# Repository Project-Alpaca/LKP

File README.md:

# LKP

レンくんピアノ (Len-kun Piano)

Capacitive touch slider controller for rhythm games.

# Contents

## pcb/LKP-Core

Microcontroller board for use with LKP electrode boards. Supports up to 32 channel of self capacitance input. Includes a WS281x LED driver channel with protection resistor. Supports I2C or UART as communication methods.

For sample firmware for use with LKP-Core, see [LKP-FW](https://github.com/Project-Alpaca/LKP-FW).

### Pin mapping

I/O port:

| \#  | Description |
| --- | ----------- |
|  1  | GND |
|  2  | INT |
|  3  | SCL/RX |
|  4  | SDA/TX |

WS281x LED connector:

| \#  | Description |
| --- | ----------- |
|  1  | GND |
|  2  | LED |

SWD connector:

| \#  | Description |
| --- | ----------- |
|  1  | VTARG |
|  2  | GND |
|  3  | RESET |
|  4  | SWCLK |
|  5  | SWDIO |

## pcb/LKP-Core-EasyAccess

**IMPORTANT**: WS281x LED driver will not work on this variant. See errata. This variant is only included for documentation purposes and will no longer receive updates.

A variant of LKP-Core that originally focused on improved accessibility for arcade controller DIY hobbyists with only basic (through hole) soldering skills. All parts used in this variant (once the chip shortage situations improve) are available for use with [JLCPCB Assembly](https://jlcpcb.com/smt-assembly) service, thus enables the possibility of ordering fully assembled and working boards straight from JLCPCB. Even without the assembly service working at the moment, the chip used in this variant can be purchased from LCSC in low quantity for a lot less money compare to the original chip on Digi-key, so it also acts as a budget option without sacrificing performance in significant ways.

## pcb/LKP-Diva-Electrode-Tile

Electrode board for Project DIVA Future Tone slider controller. Works as a 2-tile setup. Both tiles use the same design, with right tile being a 180 degree rotated version of the left tile.

## pcb/LKP-Chu-Electrode-Tile

Electrode board for Chunithm slider controller. Works the same as its LKP-Diva counterpart.

## pcb/LKP-IF-QC

I2C quick connect (compatible with SparkFun [Qwiic®][qwiic] and Adafruit [STEMMA® QT][stemmaqt]) interface for LKP-Core. Goes up to 1MHz for I2C connections and up to 24MHz for UART connections. Converts between 5V logic used by LKP-Core and 3.3V logic used by Qwiic®/STEMMA® QT.

It is also possible to use it to convert UART signal for main microcontroller running between 1.65V and 3.6V. To set it up:

1. Break out the signals on any one of the Qwiic®/STEMMA® QT port on LKP-IF-QC using a Qwiic®/STEMMA® QT breakout board.
2. Connect the 3.3V pin to microcontroller's I/O voltage reference (must be between 1.65V and 3.6V).
3. Connect SDA (blue wire, UART TX) to RX and SCL (yellow wire, UART RX) to TX.
4. The other Qwiic®/STEMMA® QT port should be left unconnected.

Note that although the low side of the level shifter can take any voltage between 1.65V and 3.6V, 3.3V must be used in order to maintain compatibility with other Qwiic®/STEMMA® QT-compatible systems.

# BOM

## LKP-Core

- **C1, C4, C6, C10**: Generic 1uF 0603 X5R ceramic capacitor. (I used `CC0603KRX5R8BB105`)
- **C2, C3, C5, C8, C11**: Generic 100nF 0603 ceramic capacitor. (I used `CL10B104KA8NNNC`)
- **C7**: `GRM2195C1H103JA01D`.
- **C9**: `GCM1885C1H222JA16D`.
- **C12**: Generic 10uF EIA-3216-18 tantalum capacitor.
- **D1**: Generic SOD-123 Schottky diode (`MBR0520L`).
- **D2**: Generic 0805 LED (yellow color).
- **FB1**: Generic 0603 ferrite bead (330ohm@100MHz).
- **J1, J2**: Straight female .1" header 2x9.
- **J3**: JST PH 2 positions.
- **J4**: Straight male .1" header 1x4 (can be angled if not using `LKP-IF-*`).
- **J5**: Straight male .1" header 1x5 (can be angled if not using `LKP-IF-*`).
- **J6**: **Angled** male .1" header 1x2.
- **R1**: Generic 1kohm 5% 0603 resistor.
- **R2**: Generic 470ohm 5% 0603 resistor.
- **R3, R4**: Generic 560ohm 5% 0603 resistor.
- **RN\***: Generic 560ohm 5% 0402x4 convex resistor array (I used `4D02WGJ0561TCE`).
- **U1**: `CY8C4246AZI-M445` (or `CY8C4247AZI-M485`, Needs minor firmware modifications).

## LKP-Diva-Electrode-Tile and LKP-Chu-Electrode-Tile

- **J1**: Straight male .1" SMD header 2x9 (**without** bumps at the bottom).
  - This can be hard to find. For small scale DIY manufacturing try searching "pin header double smd" on aliexpress.

## LKP-IF-QC

- **C1, C2**: Generic 100nF 0603 ceramic capacitor. (I used `CL10B104KA8NNNC`).
- **D1**: Generic SOD-123 Schottky diode (`MBR0520L`).
- **J1, J2**: JST SH SM04B.
- **J3**: Straight female (10.5mm stacking or regular) .1" header 1x5.
- **J4**: Straight female (10.5mm stacking or regular) .1" header 1x4.
- **J5**: Straight or angled male .1" header header 1x2 (Optional if using stacking headers for J3-4).
- **U1**: `TCA9406DCTR`.

# Powering

By default LKP expects 5V power. Using lower supply voltage down to 1.8V is possible by modifying the power specs in LKP-FW and adding a level shifter module to the WS281x driver pin (labeled as LED on board). Reference voltage for I/O can be approximated by tapping into the VTARG pin on the SWD port.

# Known issues / Erratas

- (LKP-Core v1.0) The reverse voltage protection diode (D1) does not protect C12. Proceed with caution when connecting the power to make sure the polarity is correct.
- (LKP-Core v1.1) When used with LKP-Assy, connector J4, J5 and J6 may collide with the bottom of LKP-Assy. A workaround would be soldering all the specified connectors on the back side of the PCB instead. Also, when using LKP-IF-Qwiic, J4 and J5 must be soldered on the back side.
- (LKP-Core-EasyAccess v1.2-E) Due to an oversight when choosing chips for this board, it lacks the necessary hardware features for the WS281x driver pin to function (i.e. UDB). A software workaround might be possible (with e.g. SPI DMA like FastLED Arduino library) but it might not be cost effective to develop it further.

# Special thanks

- [@pol8139][pol8139]'s [controller build guide](https://pol.booth.pm/items/967132) for pointing me to PSoC as a potential solution and demonstrating the possibility of using a single PSoC 4 to drive the entire slider.
- [@azhao12345][azhao12345] for providing the idea of modular and tiled electrode design.
- [ryun][ryun] and [@somewhatlurker][somewhatlurker] for their reverse-engineering effort on 837-15275/15330 protocol and firmware, which form the basis of LKP-Serial and [sega-slider.md](https://gist.github.com/dogtopus/b61992cfc383434deac5fab11a458597).
- [MarkH_61][markh61] for StripLightLib, which saved me quite a bit of headache of figuring out how to use UDB/datapath to drive huge array of NeoPixels without starving the CPU.

[qwiic]: https://www.sparkfun.com/qwiic
[stemmaqt]: https://learn.adafruit.com/introducing-adafruit-stemma-qt/what-is-stemma-qt
[pol8139]: https://github.com/pol8139/
[azhao12345]: https://gitlab.com/azhao12345/
[ryun]: https://ryun.halfmoon.jp/touchslider/slider_protocol.html
[markh61]: https://community.cypress.com/thread/16543
[somewhatlurker]: https://github.com/somewhatlurker

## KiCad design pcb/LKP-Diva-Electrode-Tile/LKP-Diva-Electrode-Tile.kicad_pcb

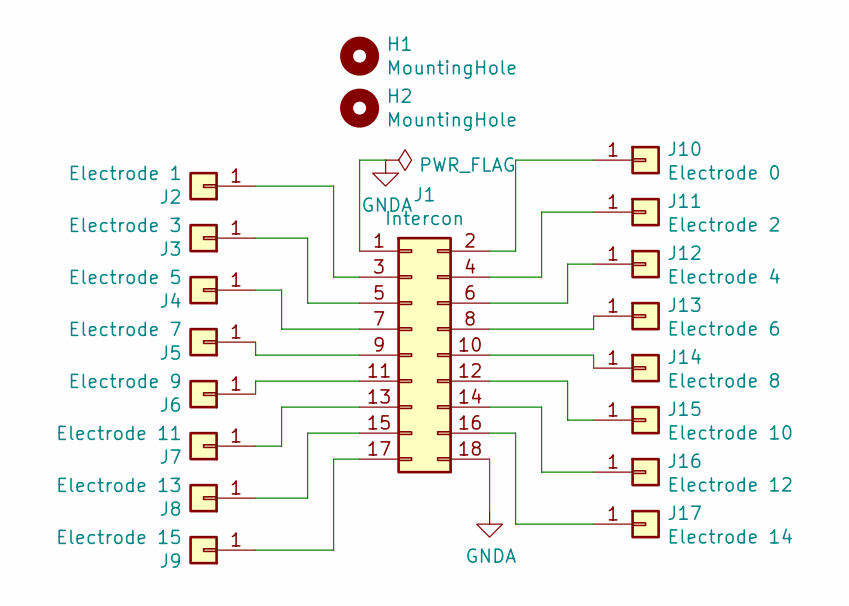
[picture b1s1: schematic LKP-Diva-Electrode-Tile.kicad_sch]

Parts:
H1, H2: MountingHole; MountingHole_3.2mm_M3_ISO7380
J1: Intercon; PinHeader_2x09_P2.54mm_Vertical_SMD
J2: Electrode 1; CapSense_Electrode_14.6x39mm
J3: Electrode 3; CapSense_Electrode_14.6x39mm
J4: Electrode 5; CapSense_Electrode_14.6x39mm
J5: Electrode 7; CapSense_Electrode_14.6x39mm
J6: Electrode 9; CapSense_Electrode_14.6x39mm
J7: Electrode 11; CapSense_Electrode_14.6x39mm
J8: Electrode 13; CapSense_Electrode_14.6x39mm
J9: Electrode 15; CapSense_Electrode_14.6x39mm
J10: Electrode 0; CapSense_Electrode_14.6x39mm
J11: Electrode 2; CapSense_Electrode_14.6x39mm
J12: Electrode 4; CapSense_Electrode_14.6x39mm
J13: Electrode 6; CapSense_Electrode_14.6x39mm
J14: Electrode 8; CapSense_Electrode_14.6x39mm
J15: Electrode 10; CapSense_Electrode_14.6x39mm
J16: Electrode 12; CapSense_Electrode_14.6x39mm
J17: Electrode 14; CapSense_Electrode_14.6x39mm

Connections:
GNDA: J1.1, J1.18
unnamed: J1.2, J10.1
unnamed: J1.3, J2.1
unnamed: J1.4, J11.1
unnamed: J1.5, J3.1
unnamed: J1.6, J12.1
unnamed: J1.7, J4.1
unnamed: J1.8, J13.1
unnamed: J1.9, J5.1
unnamed: J1.10, J14.1
unnamed: J1.11, J6.1
unnamed: J1.12, J15.1
unnamed: J1.13, J7.1
unnamed: J1.14, J16.1
unnamed: J1.15, J8.1
unnamed: J1.16, J17.1
unnamed: J1.17, J9.1

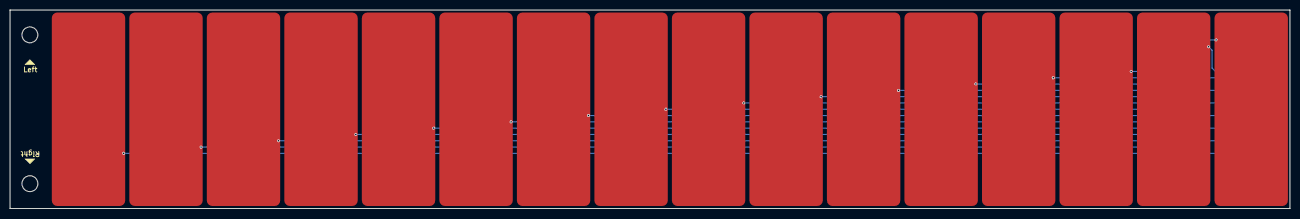
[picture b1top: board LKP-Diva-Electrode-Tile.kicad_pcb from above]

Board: 2 copper layers, 258.0 x 40.0 mm, 19 parts (1 on the bottom side), 17 nets.

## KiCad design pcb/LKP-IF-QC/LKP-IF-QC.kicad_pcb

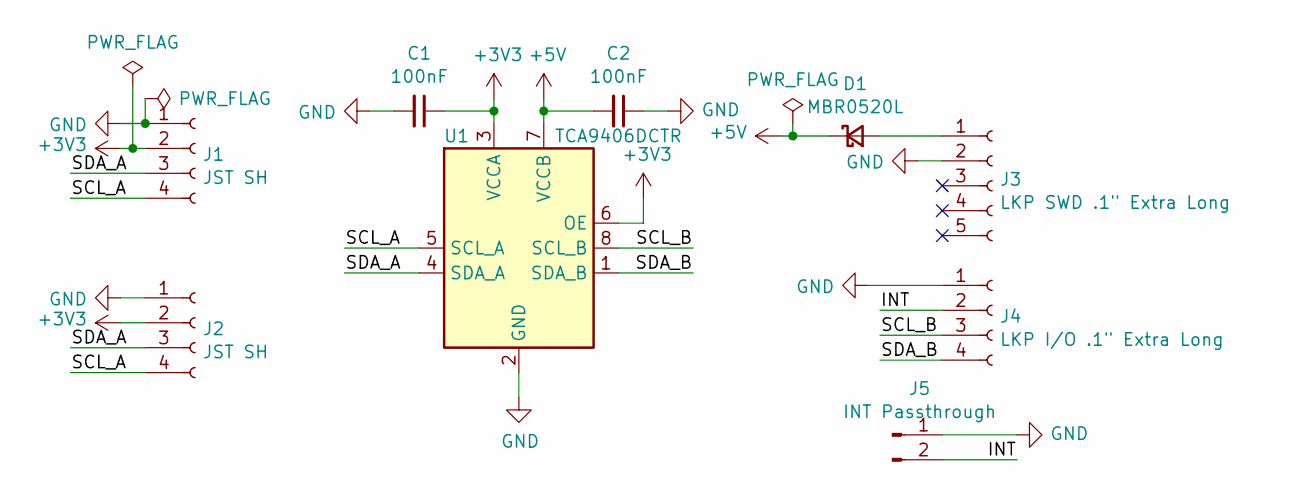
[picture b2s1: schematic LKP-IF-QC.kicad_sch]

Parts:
C1, C2: 100nF; C_0603_1608Metric
D1: MBR0520L; D_SOD-123
J1, J2: JST SH; JST_SH_SM04B-SRSS-TB_1x04-1MP_P1.00mm_Horizontal
J3: LKP SWD .1" Extra Long; PinSocket_1x05_P2.54mm_Vertical
J4: LKP I/O .1" Extra Long; PinSocket_1x04_P2.54mm_Vertical
J5: INT Passthrough; PinHeader_1x02_P2.54mm_Vertical
U1: TCA9406DCTR; SSOP-8_2.95x2.8mm_P0.65mm

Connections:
+3V3: C1.1, J1.2, J2.2, U1.3 (VCCA), U1.6 (OE)
+5V: C2.2, D1.1 (K), U1.7 (VCCB)
/INT: J4.2, J5.2
/SCL_A: J1.4, J2.4, U1.5 (SCL_A)
/SCL_B: J4.3, U1.8 (SCL_B)
/SDA_A: J1.3, J2.3, U1.4 (SDA_A)
/SDA_B: J4.4, U1.1 (SDA_B)
GND: C1.2, C2.1, J1.1, J2.1, J3.2, J4.1, J5.1, U1.2 (GND)
unnamed: D1.2 (A), J3.1

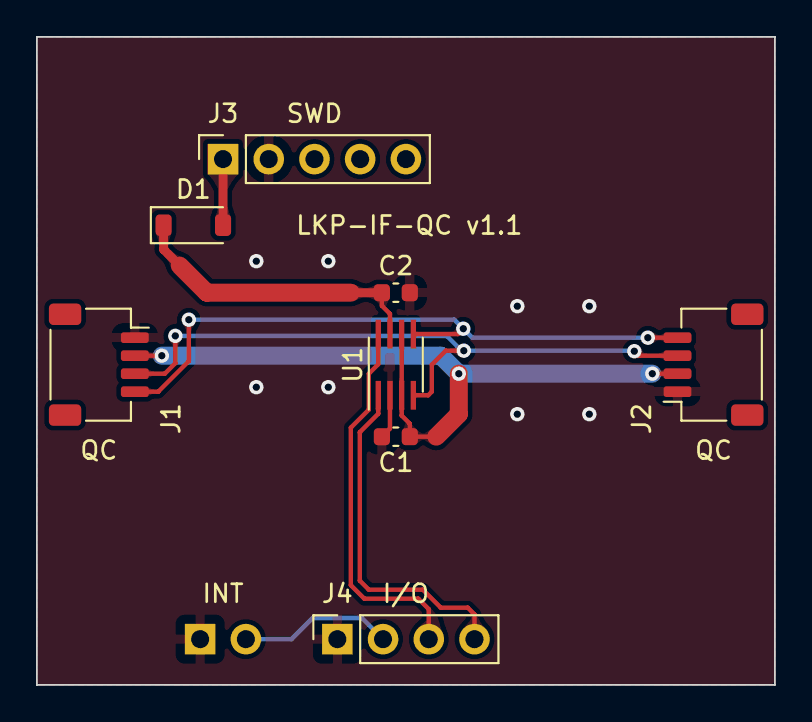
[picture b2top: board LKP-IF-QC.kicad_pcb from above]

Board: 2 copper layers, 41.0 x 36.0 mm, 9 parts (1 on the bottom side), 9 nets.

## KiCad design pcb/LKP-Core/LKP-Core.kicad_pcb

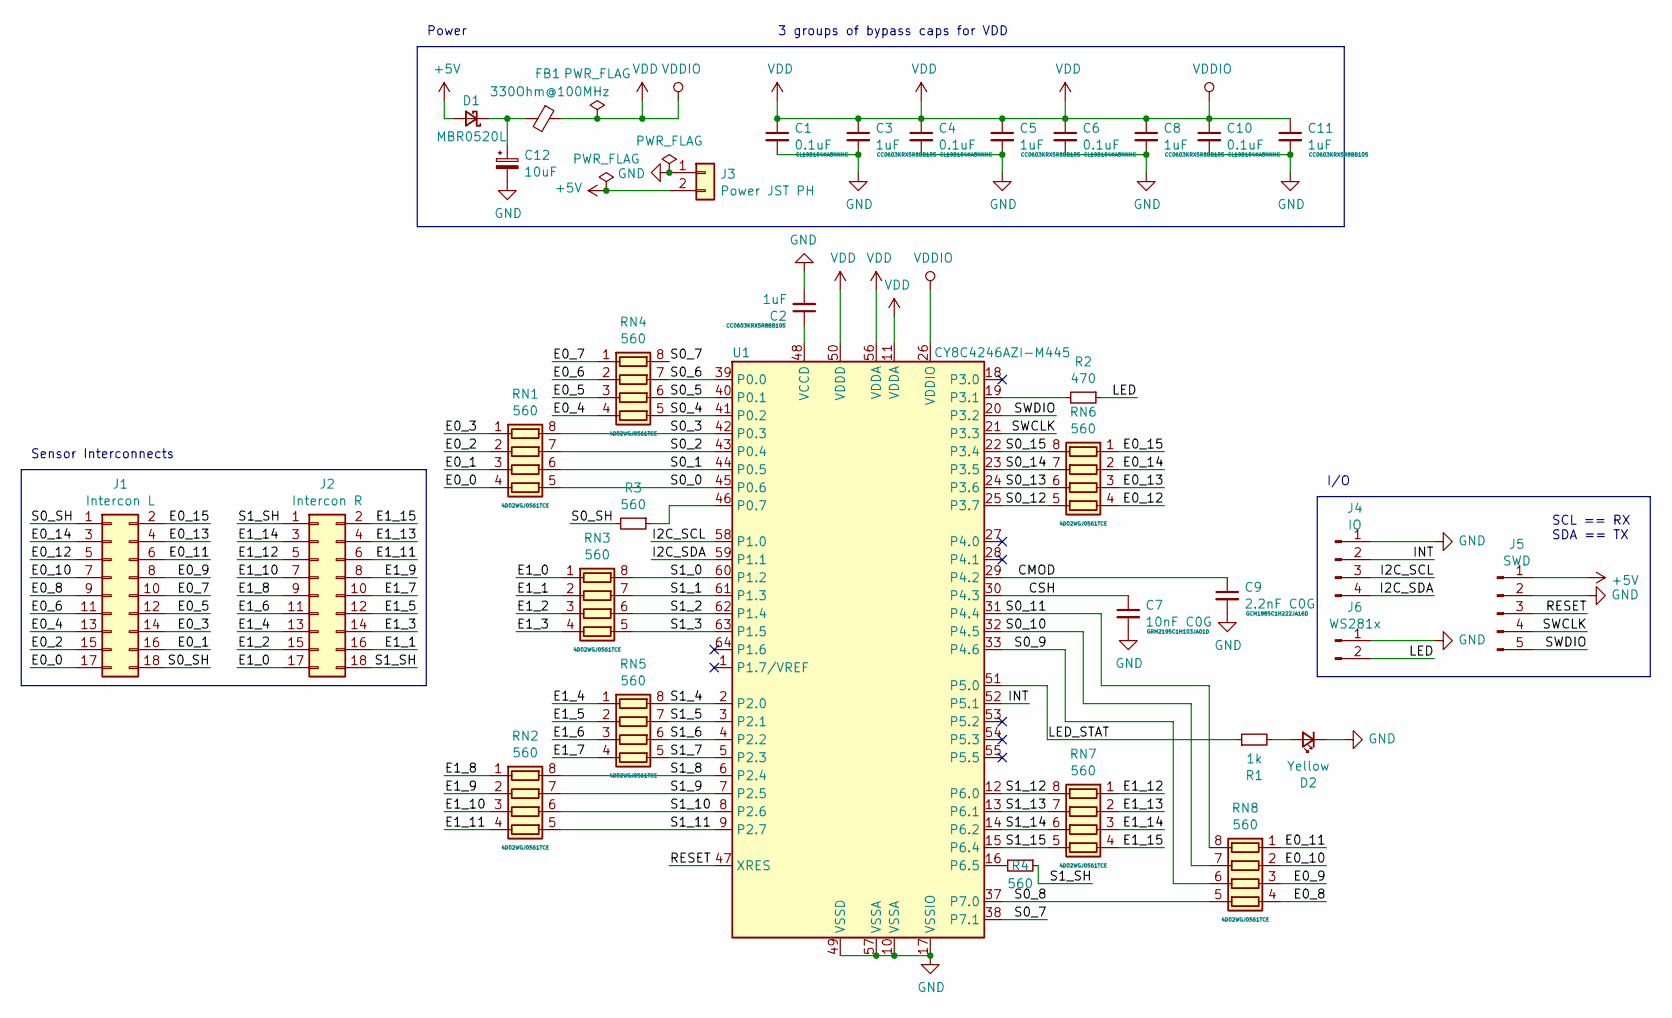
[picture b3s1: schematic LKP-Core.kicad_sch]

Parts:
C1, C4, C6, C10: 0.1uF; C_0603_1608Metric; Part Number CL10B104KA8NNNC
C2, C3, C5, C8, C11: 1uF; C_0603_1608Metric; Part Number CC0603KRX5R8BB105
C7: 10nF C0G; C_0805_2012Metric; Part Number GRM2195C1H103JA01D
C9: 2.2nF C0G; C_0603_1608Metric; Part Number GCM1885C1H222JA16D
C12: 10uF; CP_EIA-3216-18_Kemet-A
D1: MBR0520L; D_SOD-123; Part Number MBR0520L
D2: Yellow; LED_0805_2012Metric
FB1: 330Ohm@100MHz; L_0603_1608Metric
J1: Intercon L; PinSocket_2x09_P2.54mm_Vertical
J2: Intercon R; PinSocket_2x09_P2.54mm_Vertical
J3: Power JST PH; JST_PH_S2B-PH-SM4-TB_1x02-1MP_P2.00mm_Horizontal
J4: IO; PinHeader_1x04_P2.54mm_Vertical
J5: SWD; PinHeader_1x05_P2.54mm_Vertical
J6: WS281x; PinHeader_1x02_P2.54mm_Vertical
R1: 1k; R_0603_1608Metric
R2: 470; R_0603_1608Metric
R3, R4: 560; R_0603_1608Metric
RN1, RN2, RN3, RN4, RN5, RN6, RN7, RN8: 560; R_Array_Convex_4x0402; Part Number 4D02WGJ0561TCE
U1: CY8C4246AZI-M445; TQFP-64_10x10mm_P0.5mm; Part Number CY8C4246AZI-M445

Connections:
+5V: D1.2 (A), J3.2, J5.1
/CMOD: C9.1, U1.29 (P4.2)
/CSH: C7.1, U1.30 (P4.3)
/E0_0: J1.17, RN1.4 (R4.1)
/E0_1: J1.16, RN1.3 (R3.1)
/E0_2: J1.15, RN1.2 (R2.1)
/E0_3: J1.14, RN1.1 (R1.1)
/E0_4: J1.13, RN4.4 (R4.1)
/E0_5: J1.12, RN4.3 (R3.1)
/E0_6: J1.11, RN4.2 (R2.1)
/E0_7: J1.10, RN4.1 (R1.1)
/E0_8: J1.9, RN8.4 (R4.1)
/E0_9: J1.8, RN8.3 (R3.1)
/E0_10: J1.7, RN8.2 (R2.1)
/E0_11: J1.6, RN8.1 (R1.1)
/E0_12: J1.5, RN6.4 (R4.1)
/E0_13: J1.4, RN6.3 (R3.1)
/E0_14: J1.3, RN6.2 (R2.1)
/E0_15: J1.2, RN6.1 (R1.1)
/E1_0: J2.17, RN3.1 (R1.1)
/E1_1: J2.16, RN3.2 (R2.1)
/E1_2: J2.15, RN3.3 (R3.1)
/E1_3: J2.14, RN3.4 (R4.1)
/E1_4: J2.13, RN5.1 (R1.1)
/E1_5: J2.12, RN5.2 (R2.1)
/E1_6: J2.11, RN5.3 (R3.1)
/E1_7: J2.10, RN5.4 (R4.1)
/E1_8: J2.9, RN2.1 (R1.1)
/E1_9: J2.8, RN2.2 (R2.1)
/E1_10: J2.7, RN2.3 (R3.1)
/E1_11: J2.6, RN2.4 (R4.1)
/E1_12: J2.5, RN7.1 (R1.1)
/E1_13: J2.4, RN7.2 (R2.1)
/E1_14: J2.3, RN7.3 (R3.1)
/E1_15: J2.2, RN7.4 (R4.1)
/I2C_SCL: J4.3, U1.58 (P1.0)
/I2C_SDA: J4.4, U1.59 (P1.1)
/INT: J4.2, U1.52 (P5.1)
/LED: J6.2, R2.1
/LED_STAT: R1.1, U1.51 (P5.0)
/RESET: J5.3, U1.47 (XRES)
/S0_0: RN1.5 (R4.2), U1.45 (P0.6)
/S0_1: RN1.6 (R3.2), U1.44 (P0.5)
/S0_2: RN1.7 (R2.2), U1.43 (P0.4)
/S0_3: RN1.8 (R1.2), U1.42 (P0.3)
/S0_4: RN4.5 (R4.2), U1.41 (P0.2)
/S0_5: RN4.6 (R3.2), U1.40 (P0.1)
/S0_6: RN4.7 (R2.2), U1.39 (P0.0)
/S0_7: RN4.8 (R1.2), U1.38 (P7.1)
/S0_8: RN8.5 (R4.2), U1.37 (P7.0)
/S0_9: RN8.6 (R3.2), U1.33 (P4.6)
/S0_10: RN8.7 (R2.2), U1.32 (P4.5)
/S0_11: RN8.8 (R1.2), U1.31 (P4.4)
/S0_12: RN6.5 (R4.2), U1.25 (P3.7)
/S0_13: RN6.6 (R3.2), U1.24 (P3.6)
/S0_14: RN6.7 (R2.2), U1.23 (P3.5)
/S0_15: RN6.8 (R1.2), U1.22 (P3.4)
/S0_SH: J1.1, J1.18, R3.2
/S1_0: RN3.8 (R1.2), U1.60 (P1.2)
/S1_1: RN3.7 (R2.2), U1.61 (P1.3)
/S1_2: RN3.6 (R3.2), U1.62 (P1.4)
/S1_3: RN3.5 (R4.2), U1.63 (P1.5)
/S1_4: RN5.8 (R1.2), U1.2 (P2.0)
/S1_5: RN5.7 (R2.2), U1.3 (P2.1)
/S1_6: RN5.6 (R3.2), U1.4 (P2.2)
/S1_7: RN5.5 (R4.2), U1.5 (P2.3)
/S1_8: RN2.8 (R1.2), U1.6 (P2.4)
/S1_9: RN2.7 (R2.2), U1.7 (P2.5)
/S1_10: RN2.6 (R3.2), U1.8 (P2.6)
/S1_11: RN2.5 (R4.2), U1.9 (P2.7)
/S1_12: RN7.8 (R1.2), U1.12 (P6.0)
/S1_13: RN7.7 (R2.2), U1.13 (P6.1)
/S1_14: RN7.6 (R3.2), U1.14 (P6.2)
/S1_15: RN7.5 (R4.2), U1.15 (P6.4)
/S1_SH: J2.1, J2.18, R4.1
/SWCLK: J5.4, U1.21 (P3.3)
/SWDIO: J5.5, U1.20 (P3.2)
GND: C1.2, C2.2, C3.2, C4.2, C5.2, C6.2, C7.2, C8.2, C9.2, C10.2, C11.2, C12.2, D2.1 (K), J3.1, J4.1, J5.2, J6.1, U1.10 (VSSA), U1.17 (VSSIO), U1.49 (VSSD), U1.57 (VSSA)
unnamed: C12.1, D1.1 (K), FB1.2
unnamed: D2.2 (A), R1.2
unnamed: R3.1, U1.46 (P0.7)
unnamed: R2.2, U1.19 (P3.1)
unnamed: R4.2, U1.16 (P6.5)
unnamed: C2.1, U1.48 (VCCD)
VDD: C1.1, C3.1, C4.1, C5.1, C6.1, C8.1, C10.1, C11.1, FB1.1, U1.11 (VDDA), U1.26 (VDDIO), U1.50 (VDDD), U1.56 (VDDA)

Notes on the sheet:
Sensor Interconnects
I/O
SCL == RX SDA == TX
Power
3 groups of bypass caps for VDD

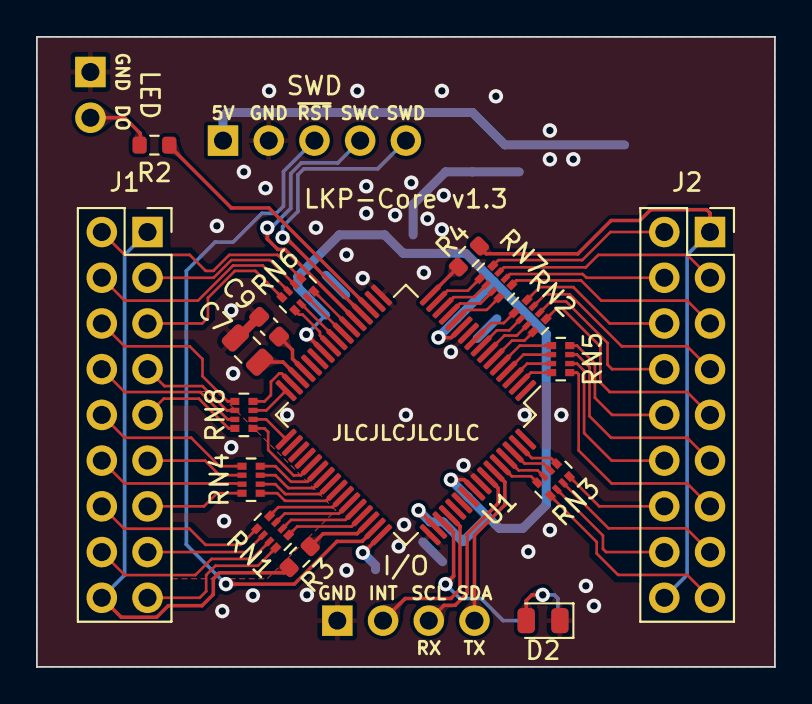
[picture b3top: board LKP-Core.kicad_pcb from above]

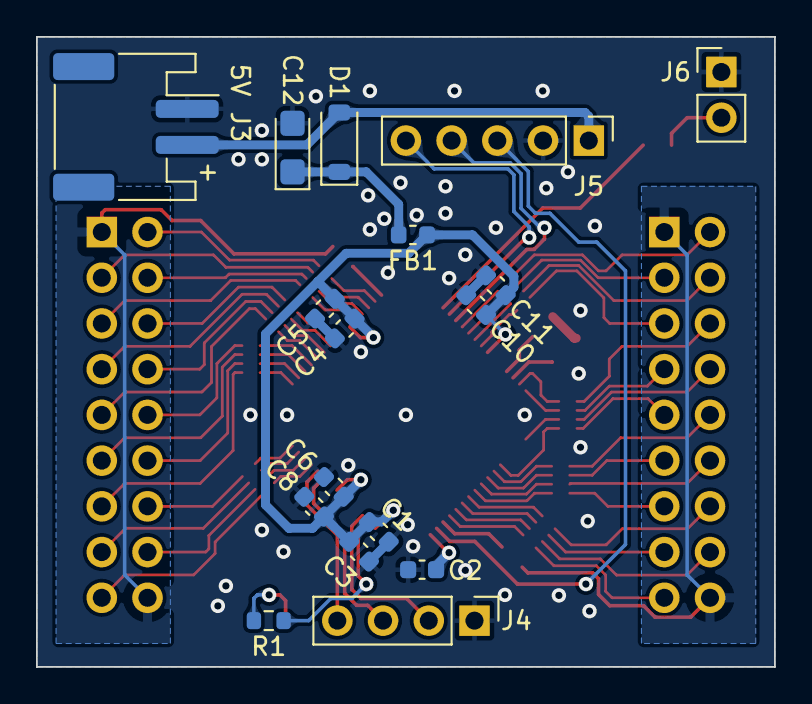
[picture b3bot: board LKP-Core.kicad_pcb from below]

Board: 2 copper layers, 41.0 x 35.0 mm, 34 parts (17 on the bottom side), 85 nets.

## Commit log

2019-07-27 Initial layout on diva electrode tile
2019-07-29 Start working on LKP-Core
2019-08-03 Fix sensor topology
2019-08-03 Iteration 1.1 routing
2019-08-03 Add measurement
2019-08-03 LKP-Core WIP
2019-08-04 Finish schematic
2019-08-04 Misc changes to schematic
2019-08-04 Fix right shield
2019-08-05 Initial placement plan
2019-08-05 Define net classes
2019-08-05 Power routing plan
2019-08-06 Power line routing
2019-08-06 Sensor routing
2019-08-06 Finishing up
2019-08-07 Move various IO pins down
2019-08-07 Apply changes
2019-08-07 Misc
2019-08-08 Refactor right side routing
2019-08-08 Finish up
2019-08-08 Some finishing touches
2019-08-08 Fab layer fixes
2019-08-08 Add the status LED back
2019-08-08 Cleanup
2019-08-08 MOAR VIAS
2019-08-09 Add resistors for shield
2019-08-09 Switch to through hole headers and add a capacitor for good luck
2019-08-17 Derp
2019-08-17 Why not?
2019-08-17 Add license
2019-09-02 Clarify that kicad 6 == nightly
2020-01-31 Finish routing.
2020-01-31 Place screw holes.
2020-01-31 Copy-paste schematic from LKP-Diva with some necessary changes
2020-01-31 Copper fills and fix solder mask on electrodes
2020-01-31 Add direction indicator.
2020-02-02 Update board dimension marker
2020-02-02 Add dimension PDFs for easier reference
2020-09-26 Make reverse voltage protection also work with the tantalum filter cap.
    Bump LKP-Core version number
2020-09-26 Add LKP-Core board preview to README
2020-10-24 Add simple BOM and errata section
2020-10-24 Add note about the protection diode issue on LKP-Core v1.0
2020-11-10 C1, C4, C6, C10 should be 1uF
2021-02-27 More info about powering
2021-03-01 Add schematic for LKP-IF-Qwiic
2021-03-03 LKP-IF-Qwiic: Add board.
    LKP-Core: Add more measurements.
2021-03-03 Add info about LKP-IF-Qwiic. Add pin mapping table.
2021-03-03 Properly define the "3.3V" Qwiic Vref according to TCA9406 datasheet.
2021-03-03 Add logo
2021-03-03 Properly set alt text
2021-03-03 LKP-IF-Qwiic: Add reverse voltage protection.
2021-03-03 Add reverse voltage protection diode to LKP-IF-Qwiic BOM
2021-03-03 Minor routing adjustment.
2021-03-04 LKP-IF-Qwiic: Add INT passthrough connector as an alternative to stacking headers.
    README: Add notes about how to find the hard-to-find 18-pin male header.
2021-03-04 README: Add notes about stacking headers.
2021-03-04 README: Add extra notes about LKP-IF-Qwiic compatibility with LKP-Core <= 1.1
2021-03-14 LKP-Core: Change schematics so the status LED is directly connected to PSoC pin for better readability.
2021-03-14 LKP-Core: Add more descriptive silkscreens.
2021-03-14 D -> DO
2021-03-14 LKP-Core: Change minimum mask width and clearance to 0. Slight GND via rearrangements.
2021-03-14 docs: Add LKP-Core dimensions. Update preview pic.
2021-03-19 Notches -> bumps
2021-03-21 Mention LKP-FW in README.
2021-03-21 LKP-Diva-Electrode-Tile: Update to new format.
    - Update hatched fill.
    - Increase the electrode size to 14.6x39mm.
    - Change routing to fit the new pad size.
    - Bump version number.
2021-03-21 Also update LKP-Chu-Electrode-Tile.
2021-03-21 Update README.
2021-03-22 Bump versions for LKP-Chu-Electrode-Tile.
2021-03-28 Add CY8C4147AZI-S455 to LKP-Core symbol library.
2021-03-28 Update datasheet reference
2021-03-28 Add LKP-Core-EasyAccess.
    It's derived from LKP-Core with all used parts available for use with JLCPCB
    assembly service. Specifically the PSoC is replaced with the newer PSoC 4100S
    series.
    Since JLCPCB still don't support double sided SMD assembly, this will remain
    as not ready for publishing for now.
2021-04-15 LKP-Core: Add top to PSoC measurement.
2021-04-21 Add JLCPCB batch identifier location to LKP-Core.
2021-07-26 README: clarify what the new variant actually do currently
2021-07-30 Add notes about the component choosing screwup.
    PSoC 4100S series don't have UDB so WS281x LED driver based on StripLightLib will not work. This variant will probably be discontinued or at least not developed further.
2022-01-02 Update all active projects to KiCad 6.
2023-06-23 Update electrode tile projects to KiCad 7
2023-06-23 Minor adjustments to LKP-Core and release v1.3
    - Move LKP-Core to KiCad 7
    - Add teardrop to everything except on intercon connectors.
    - Use regular LED footprint instead of the accidentally added castellated one (somewhat a duplicate of handsoldering but slightly larger)
    - Move to mainline PSoC symbol
2023-06-23 Update LKP-IF-Qwiic and bump version to v1.1
    - Rename the project from LKP-IF-Qwiic to LKP-IF-QC since Qwiic isn't the only name for this connector.
    - Move to KiCad 7.
    - Enable teardrops.
    - Minor routing tweaks. No schematic change.
2023-06-30 v4.2
    Unify export settings across projects
2023-07-09 Add a special thanks section
